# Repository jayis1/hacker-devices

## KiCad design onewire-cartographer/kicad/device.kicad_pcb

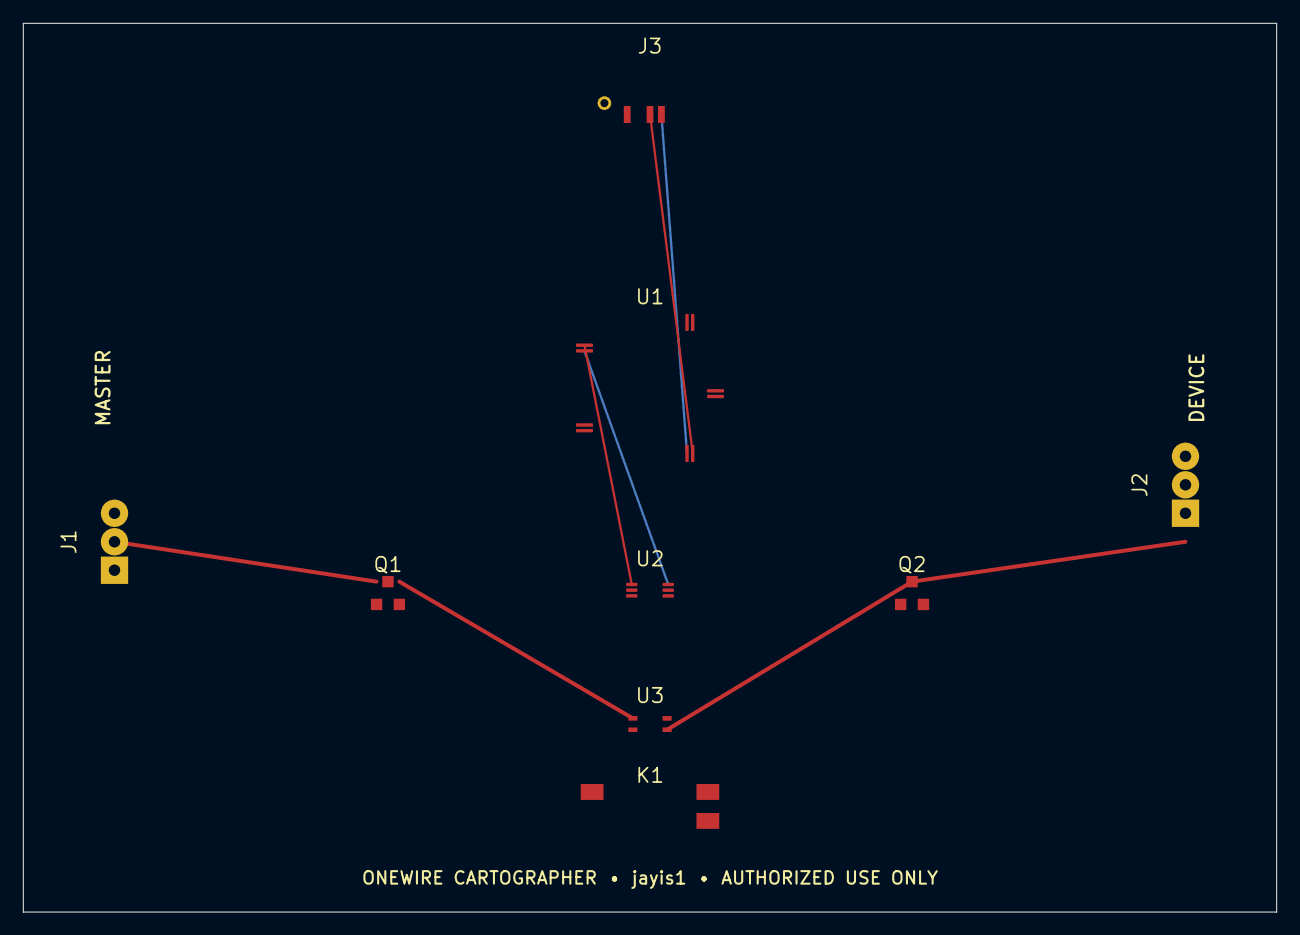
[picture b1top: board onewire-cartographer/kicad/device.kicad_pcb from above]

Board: 4 copper layers, 110.0 x 78.0 mm, 9 parts (0 on the bottom side), 12 nets.

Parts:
J1: MASTER; JST_XH_B3B-XH-A_1x03_P2.50mm_Vertical
J2: DEVICE; JST_XH_B3B-XH-A_1x03_P2.50mm_Vertical
J3: USB-C; USB_C_Receptacle_GCT_USB4105-xx-A_16P_TopMnt_Horizontal
K1: NC FAIL-OPEN BYPASS; Relay_DPDT_Omron_G6K-2F-Y
Q1, Q2: 2N7002; SOT-23
U1: STM32G474RET6; LQFP-64_10x10mm_P0.5mm
U2: TLV3502; VSSOP-8_2.3x2mm_P0.5mm
U3: TS5A23157; Texas_DRC0010J

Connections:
+3V3: U1.63, U2.3, U2.8, U3.10
+5V_LIMITED: J1.1, J2.1
BRIDGE_ENABLE: K1.4, U1.25, U3.3
DEVICE_EDGE: U1.2, U2.7
DEVICE_PULL_GATE: Q2.1, U1.16
GND: J1.3, J2.3, J3.A1, Q1.2, Q2.2, U1.64
MASTER_EDGE: U1.1, U2.1
MASTER_PULL_GATE: Q1.1, U1.15
OW_DEVICE_DQ: J2.2, K1.8, Q2.3, U2.5, U3.8
OW_MASTER_DQ: J1.2, K1.1, Q1.3, U2.2, U3.1
USB_DM: J3.A7, U1.34
USB_DP: J3.A6, U1.33

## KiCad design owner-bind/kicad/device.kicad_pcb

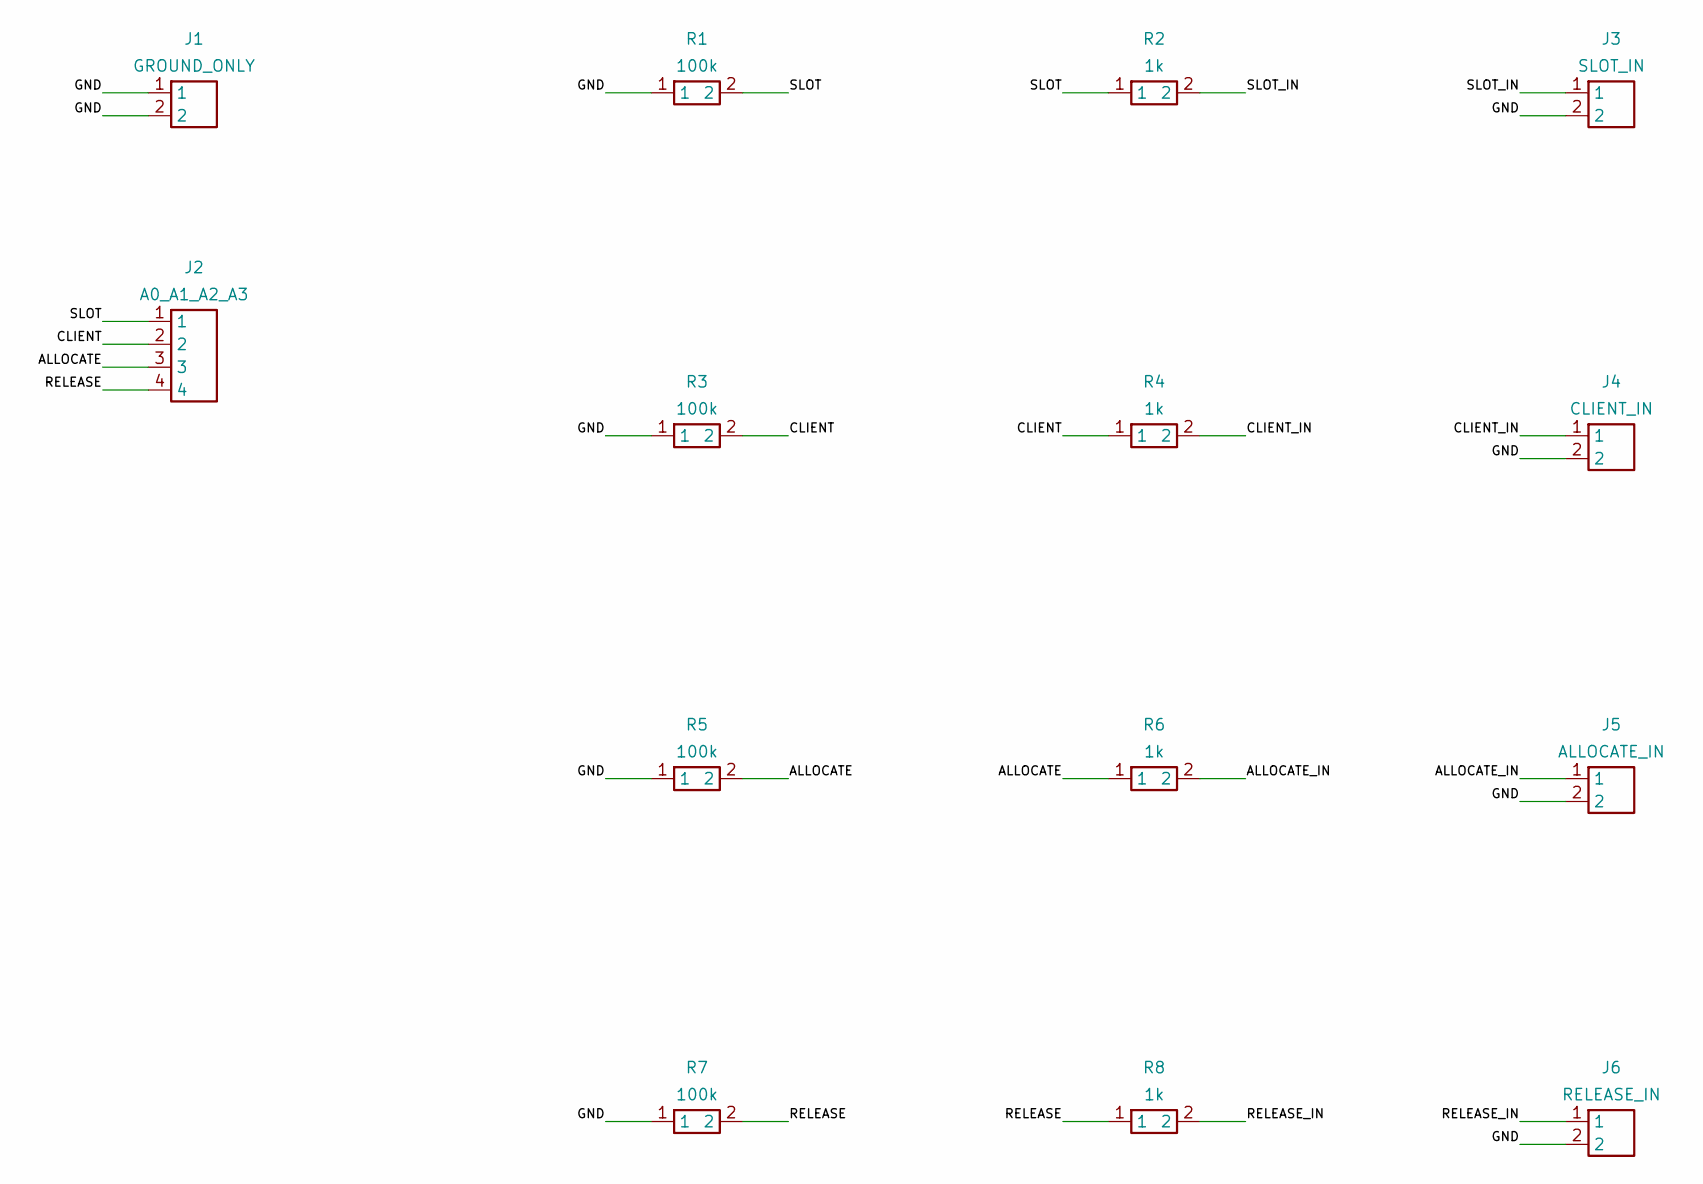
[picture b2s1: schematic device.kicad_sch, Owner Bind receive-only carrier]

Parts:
J1: GROUND_ONLY; PinHeader_1x02_P2.54mm_Vertical
J2: A0_A1_A2_A3; PinHeader_1x04_P2.54mm_Vertical
J3: SLOT_IN; PinHeader_1x02_P2.54mm_Vertical
J4: CLIENT_IN; PinHeader_1x02_P2.54mm_Vertical
J5: ALLOCATE_IN; PinHeader_1x02_P2.54mm_Vertical
J6: RELEASE_IN; PinHeader_1x02_P2.54mm_Vertical
R1, R3, R5, R7: 100k; R_Axial_DIN0207_L6.3mm_D2.5mm_P7.62mm_Horizontal
R2, R4, R6, R8: 1k; R_Axial_DIN0207_L6.3mm_D2.5mm_P7.62mm_Horizontal

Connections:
ALLOCATE: J2.3, R5.2, R6.1
ALLOCATE_IN: J5.1, R6.2
CLIENT: J2.2, R3.2, R4.1
CLIENT_IN: J4.1, R4.2
GND: J1.1, J1.2, J3.2, J4.2, J5.2, J6.2, R1.1, R3.1, R5.1, R7.1
RELEASE: J2.4, R7.2, R8.1
RELEASE_IN: J6.1, R8.2
SLOT: J2.1, R1.2, R2.1
SLOT_IN: J3.1, R2.2

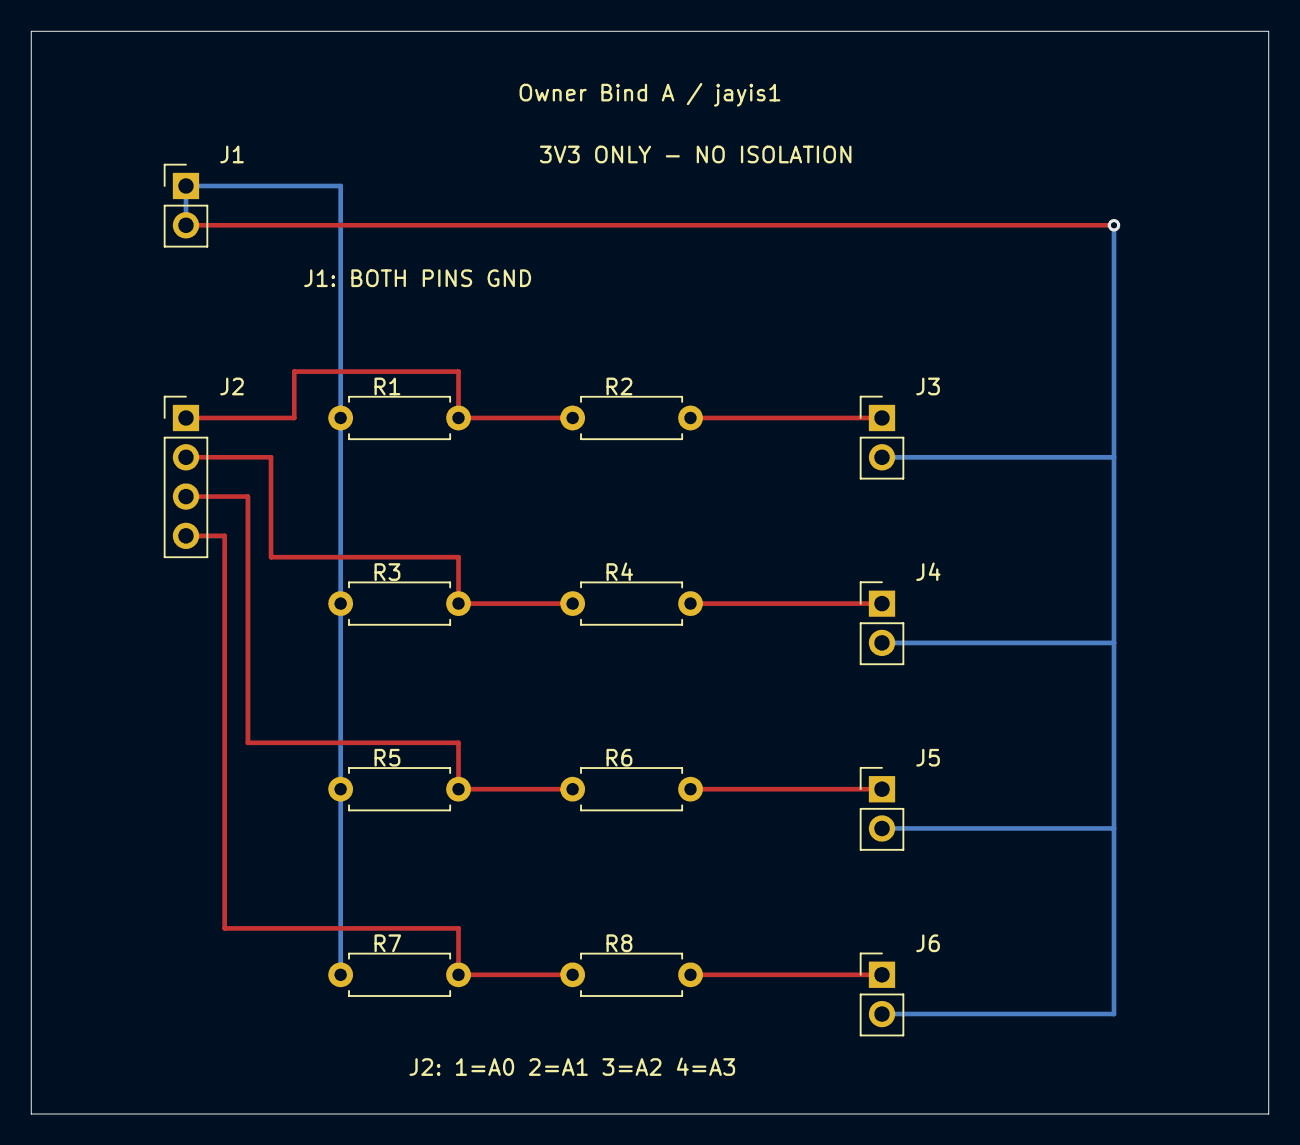
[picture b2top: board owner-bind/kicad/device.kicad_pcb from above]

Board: 2 copper layers, 80.0 x 70.0 mm, 14 parts (0 on the bottom side), 9 nets.

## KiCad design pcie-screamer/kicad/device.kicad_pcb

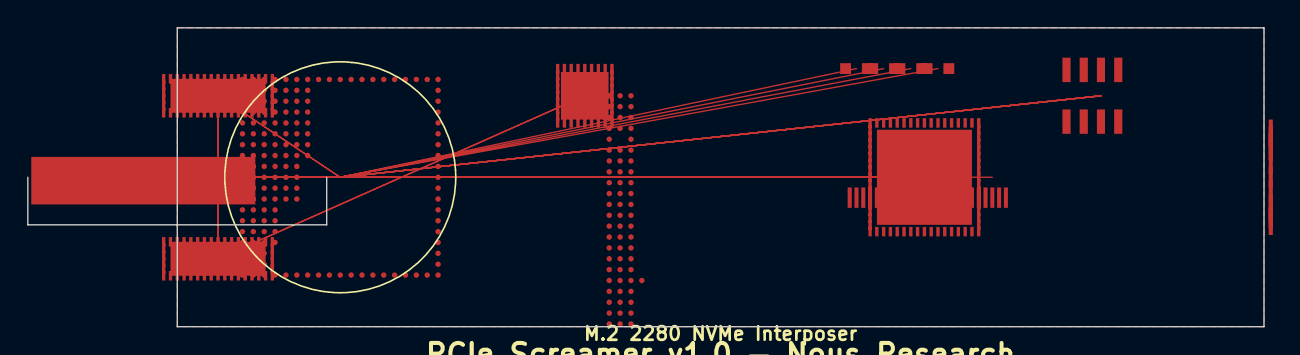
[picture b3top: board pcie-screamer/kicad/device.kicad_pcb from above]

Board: 8 copper layers, 80.0 x 22.0 mm, 14 parts (0 on the bottom side), 70 nets.

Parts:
D1: Green; LED_0603_1608Metric
D2: Blue; LED_0603_1608Metric
D3: Amber; LED_0603_1608Metric
D4: Red; LED_0603_1608Metric
J1: M.2_M-Key_Edge; M2_Edge_M_Key
J2: 10132797-0011LF; M2_Socket_M_Key
J3: TYPE-C-31-M-12; USB_C_Receptacle_16pin
U1: LFE5U-45F-6BG381C; BGA-381_17.0x17.0mm_Layout19x19_P0.8mm
U2, U3: PI3EQX12908ZHE; TQFN-42-1EP_9x3.5mm_P0.5mm
U4: FT601Q-B-T; QFN-76-1EP_9x9mm_P0.5mm
U5: MT41K256M16TW-107; FBGA-96_9.0x14.0mm_Layout9x16_P0.8mm
U6: W25Q128JVSIQ; SOIC-8_5.23x5.23mm_P1.27mm
U7: Si5332A-D-GM1; QFN-32-1EP_5x5mm_P0.5mm

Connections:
+1V2: U1.VCCIO_B4_5_7, U4.47, U4.48, U4.62, U4.63
+1V8: U1.VCCAUX, U1.VCCA_PLL
+1V35: U1.VCCIO_B6, U5.B7, U5.D3, U5.D8, U5.E1, U5.F9, U5.G1, U5.G9, U5.H1, U5.H9, U5.L1, U5.L9, U5.M1, U5.M9, U5.N1, U5.N9, U5.P1, U5.P9, U5.R1, U5.R9
+3V3: J1.2, J1.4, J1.70, J1.72, J1.74, J2.3V3, U1.C6, U1.C7, U1.D6, U1.D7, U1.E2, U1.F2, U1.G2, U1.H2, U1.J2, U1.K2, U1.L2, U1.M2, U1.VCCIO_B0_3, U2.1, U2.11, U2.21, U2.31, U3.1, U3.11, U3.21, U3.31, U4.5, U4.6, U4.7, U4.8, U4.9, U4.43, U4.44, U6.3, U6.7, U6.8, U7.5, U7.6, U7.7, U7.8
+3V3A: U4.49, U4.50
+5V0: J3.VBUS, U4.55
CLKREQ#: J1.52, J2.CLKREQ#, U1.AR2, U1.D5
DDR3_A[14:0]: U1.AA1, U1.AA2, U1.AA3, U1.U1, U1.U2, U1.U3, U1.V1, U1.V2, U1.V3, U1.W1, U1.W2, U1.W3, U1.Y1, U1.Y2, U1.Y3, U5.L7, U5.M2, U5.M3, U5.M7, U5.N2, U5.N3, U5.N7, U5.N8, U5.P3, U5.P8, U5.R3, U5.R7, U5.R8, U5.T3, U5.T8
DDR3_BA[2:0]: U1.AB1, U1.AB2, U1.AB3, U5.M6, U5.P2, U5.P7
DDR3_CAS#: U1.AM1, U5.K3
DDR3_CKE: U1.AL1, U5.K9
DDR3_CK_N: U1.AK3, U5.J7
DDR3_CK_P: U1.AK2, U5.K7
DDR3_CS#: U1.AL2, U5.L2
DDR3_DM[1:0]: U1.AJ3, U1.AK1, U5.D1, U5.E3
DDR3_DQS0_N: U1.AH3, U5.F3
DDR3_DQS0_P: U1.AH2, U5.F2
DDR3_DQS1_N: U1.AJ2, U5.B3
DDR3_DQS1_P: U1.AJ1, U5.B2
DDR3_DQ[15:0]: U1.AC1, U1.AC2, U1.AC3, U1.AD1, U1.AD2, U1.AD3, U1.AE1, U1.AE2, U1.AE3, U1.AF1, U1.AF2, U1.AF3, U1.AG1, U1.AG2, U1.AG3, U1.AH1, U5.A2, U5.A3, U5.A7, U5.A8, U5.B1, U5.B8, U5.C2, U5.C3, U5.C8, U5.D7, U5.E7, U5.E8, U5.F7, U5.F8, U5.G7, U5.G8
DDR3_ODT: U1.AM3, U5.K1
DDR3_RAS#: U1.AL3, U5.J3
DDR3_RESET#: U1.AN1, U5.T2
DDR3_WE#: U1.AM2, U5.L3
FT_BE[3:0]: U1.E7, U1.F7, U1.G7, U1.H7, U4.18, U4.70, U4.71, U4.76
FT_CLK: U1.M1, U4.35
FT_D[31:0]: U1.E3, U1.E4, U1.E5, U1.E6, U1.F3, U1.F4, U1.F5, U1.F6, U1.G3, U1.G4, U1.G5, U1.G6, U1.H3, U1.H4, U1.H5, U1.H6, U1.J3, U1.J4, U1.J5, U1.J6, U1.K3, U1.K4, U1.K5, U1.K6, U1.L3, U1.L4, U1.L5, U1.L6, U1.M3, U1.M4, U1.M5, U1.M6, U4.1, U4.2, U4.3, U4.4, U4.10, U4.11, U4.12, U4.13, U4.14, U4.15, U4.16, U4.17, U4.19, U4.20, U4.21, U4.22, U4.23, U4.24, U4.25, U4.26, U4.27, U4.28, U4.29, U4.30, U4.31, U4.32, U4.33, U4.34, U4.72, U4.73, U4.74, U4.75
FT_OE#: U1.J1, U4.42
FT_RD#: U1.H1, U4.41
FT_RESET#: U1.L1, U4.36
FT_RXF#: U1.F1, U4.39
FT_SIWU#: U1.K1, U4.37
FT_TXE#: U1.E1, U4.38
FT_WR#: U1.G1, U4.40
GND: D1.2, D2.2, D3.2, D4.2, J1.1, J1.3, J1.9, J1.15, J1.21, J1.27, J1.33, J1.39, J1.45, J1.51, J1.57, J1.71, J1.73, J1.75, J2.GND, J3.CC1, J3.CC2, J3.GND, J3.GND2, U1.A1, U1.A2, U1.B1, U1.B2, U1.C1, U1.C2, U1.D1, U1.D2, U2.6, U2.16, U2.26, U2.36, U2.EP, U3.6, U3.16, U3.26, U3.36, U3.EP, U4.45, U4.46, U4.51, U4.52, U4.56, U4.57, U4.58, U4.59, U4.60, U4.61, U4.64, U4.65, U4.67, U4.69, U4.EP, U5.A1, U5.A9, U5.B9, U5.C1, U5.C9, U5.D2, U5.D9, U5.E9, U5.F1, U5.G2, U5.G3, U5.H2, U5.H3, U5.H7, U5.H8, U5.J2, U5.J8, U5.J9, U5.K2, U5.K8, U5.L8, U5.M8, U5.R2, U5.T1, U5.T9, U6.4, U7.1, U7.2, U7.3, U7.4, U7.9, U7.10, U7.11, U7.12, U7.13, U7.14, U7.15, U7.16, U7.17, U7.18, U7.19, U7.20, U7.21, U7.22, U7.23, U7.24, U7.27, U7.28, U7.31, U7.32, U7.EP
I2C_SCL: U1.A6, U1.A7, U2.41, U3.41, U7.25
I2C_SDA: U1.B6, U1.B7, U2.42, U3.42, U7.26
LED0: D1.1, U1.A4
LED1: D2.1, U1.B4
LED2: D3.1, U1.C4
LED3: D4.1, U1.D4
PCIE_REFCLK_N: J1.53, J2.REFCLKn, U1.AP2, U7.29
PCIE_REFCLK_P: J1.55, J2.REFCLKp, U1.AP1, U7.30
PCIE_RX0_N: J1.41, J2.PERn0, U1.N2, U2.3, U2.5
PCIE_RX0_P: J1.43, J2.PERp0, U1.N1, U2.2, U2.4
PCIE_RX1_N: J1.29, J2.PERn1, U1.N4, U2.8, U2.10, U2.33, U2.35
PCIE_RX1_P: J1.31, J2.PERp1, U1.N3, U2.7, U2.9, U2.32, U2.34
PCIE_RX2_N: J1.17, J2.PERn2, U1.R2, U3.3, U3.5
PCIE_RX2_P: J1.19, J2.PERp2, U1.R1, U3.2, U3.4
PCIE_RX3_N: J1.5, J2.PERn3, U1.R4, U3.8, U3.10, U3.33, U3.35
PCIE_RX3_P: J1.7, J2.PERp3, U1.R3, U3.7, U3.9, U3.32, U3.34
PCIE_TX0_N: J1.47, J2.PETn0, U1.P2, U2.13, U2.15, U2.23, U2.25
PCIE_TX0_P: J1.49, J2.PETp0, U1.P1, U2.12, U2.14, U2.22, U2.24
PCIE_TX1_N: J1.35, J2.PETn1, U1.P4, U2.18, U2.20, U2.28, U2.30, U2.38, U2.40
PCIE_TX1_P: J1.37, J2.PETp1, U1.P3, U2.17, U2.19, U2.27, U2.29, U2.37, U2.39
PCIE_TX2_N: J1.23, J2.PETn2, U1.T2, U3.13, U3.15, U3.23, U3.25
PCIE_TX2_P: J1.25, J2.PETp2, U1.T1, U3.12, U3.14, U3.22, U3.24
PCIE_TX3_N: J1.11, J2.PETn3, U1.T4, U3.18, U3.20, U3.28, U3.30, U3.38, U3.40
PCIE_TX3_P: J1.13, J2.PETp3, U1.T3, U3.17, U3.19, U3.27, U3.29, U3.37, U3.39
PERST#: J1.50, J2.PERST#, U1.AR1, U1.C5
PEWAKE#: J1.54, J2.PEWAKE#, U1.AR3
SPI_CLK: U1.B3, U6.6
SPI_CS#: U1.A3, U6.1
SPI_MISO: U1.D3, U6.2
SPI_MOSI: U1.C3, U6.5
SUSCLK: J1.68, J2.SUSCLK
USB_DM: J3.D-, U4.53
USB_DP: J3.D+, U4.54
USB_SSRX_N: J3.SSRX-, U4.66
USB_SSRX_P: J3.SSRX+, U4.68

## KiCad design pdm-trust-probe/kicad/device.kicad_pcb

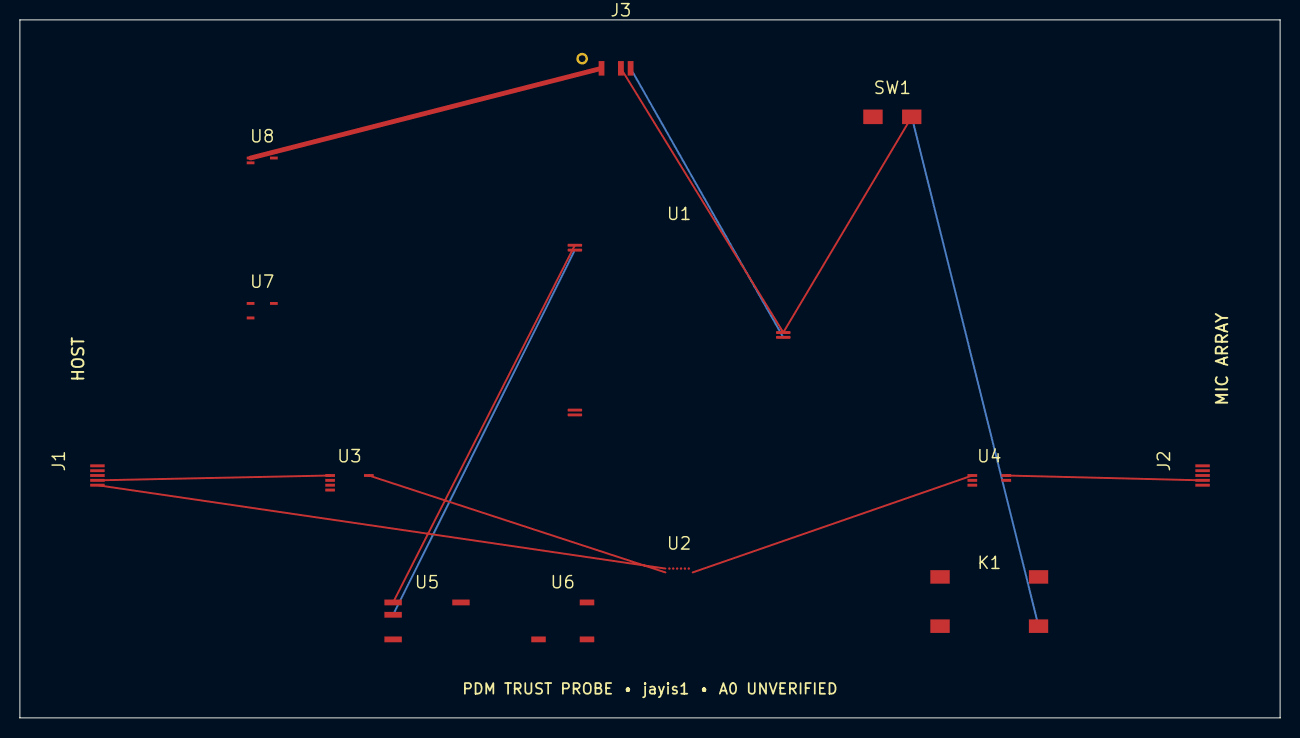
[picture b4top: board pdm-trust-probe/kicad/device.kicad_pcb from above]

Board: 4 copper layers, 130.0 x 72.0 mm, 13 parts (0 on the bottom side), 13 nets.

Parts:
J1: HOST PDM; TE_1-1734592-0_1x10-1MP_P0.5mm_Horizontal
J2: MIC PDM; TE_1-1734592-0_1x10-1MP_P0.5mm_Horizontal
J3: USB-C; USB_C_Receptacle_GCT_USB4105-xx-A_16P_TopMnt_Horizontal
K1: FAIL-SAFE BYPASS; Relay_DPDT_Omron_G6K-2F-Y
SW1: PHYSICAL ARM; SW_SPST_TL3301AN
U1: STM32H563ZIT6; LQFP-144_20x20mm_P0.5mm
U2: iCE40UP5K-SG48; ucBGA-48_3.0x3.0mm_Layout6x8_P0.4mm
U3: SN74AXC4T245; UQFN-14-1EP_3.5x2.5mm_P0.5mm_EP0.6x2.6mm
U4: TMUX1574; WQFN-16-1EP_3x3mm_P0.5mm_EP1.75x1.75mm
U5: MX25L12835F; SOIC-8_5.23x5.23mm_P1.27mm
U6: ATECC608B; SOIC-8_3.9x4.9mm_P1.27mm
U7: ADS7042; WSON-8-1EP_2x2mm_P0.5mm_EP0.6x1.2mm
U8: TPS62172; WSON-8-1EP_2x2mm_P0.5mm_EP0.6x1.2mm

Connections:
+3V3: U1.143, U3.14, U5.8, U6.8, U7.8, U8.8
GND: J3.A1, K1.2, SW1.1, U1.144, U5.4, U6.4, U7.4, U8.2
PATTERN_ENABLE: K1.7, SW1.2, U4.15
PDM_CLK: J1.1, J2.1, K1.1, K1.8, U2.A1
PDM_DATA0: J1.2, J2.2, U2.B1, U3.2, U4.1
PDM_DATA1: J1.3, J2.3, U2.C1, U3.3, U4.2
PDM_DATA2: J1.4, J2.4, U2.D1, U3.4, U4.3
PDM_DATA3: J1.5, J2.5, U2.E1, U3.5, U4.14
SPI_CLK: U1.1, U5.1
SPI_DATA: U1.2, U5.2, U6.5
USB_DM: J3.A7, U1.71
USB_DP: J3.A6, U1.70
VBUS: J3.A4, U8.1

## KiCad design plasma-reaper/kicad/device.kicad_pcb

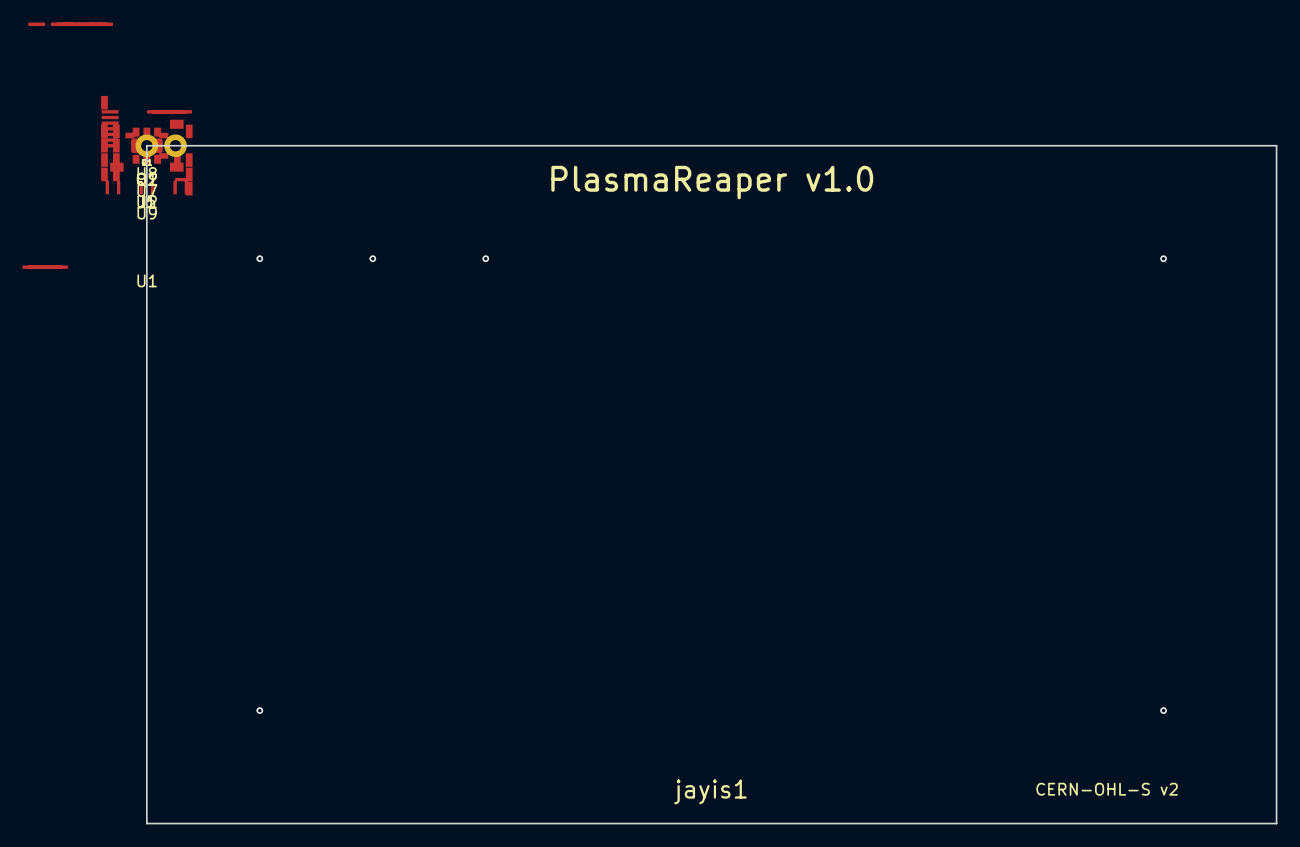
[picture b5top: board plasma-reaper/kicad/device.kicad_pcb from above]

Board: 2 copper layers, 100.0 x 60.0 mm, 11 parts (0 on the bottom side), 17 nets.

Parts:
C1: 100nF; C_0603_1608Metric
J1: USB_C_Receptacle; USB_C_Receptacle_HRO_TYPE-C-31-M-12
J5: BNC; BNC_Amphenol_031-6535_Horizontal
Q1: SiS413DN; PowerPAK_1212-8_Single
Q2: BSC060N10NS3G; TDSON-8-1
R1: 0R5; R_0805_2012Metric
U1: STM32H723ZGT6; LQFP-144_20x20mm_P0.5mm
U2: iCE40UP5K-SG48; QFN-48-1EP_7x7mm_P0.5mm_EP5.6x5.6mm
U7: ZXGD3004E1; SOIC-8_3.9x9.9mm_P1.27mm
U8: DAC5311; SOT-23-6
U9: TS3A5018; SOIC-16_3.9x9.9mm_P1.27mm

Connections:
+3V3: C1.1, U1.11, U1.19, U1.28, U1.30, U2.1, U8.3, U9.16
+5V: Q2.2, U7.1
EM_COIL+: J5.1, U7.6
EM_COIL-: J5.2, U7.4
EM_GATE: U2.5, U7.2
FPGA_NSS: U1.39, U2.28
GND: C1.2, J1.A1, J1.B1, Q1.2, U1.10, U1.27, U1.29, U1.49, U2.24, U7.3, U8.4, U9.8
MUX_SEL0: U2.6, U9.14
MUX_SEL1: U2.7, U9.13
SHUNT_GATE: Q1.1, U2.4
SPI1_MISO: U1.41, U2.25
SPI1_MOSI: U1.42, U2.26, U8.2
SPI1_SCK: U1.40, U2.27, U8.1
USB_DM: J1.A7, U1.46
USB_DP: J1.A6, U1.47
VBUS: J1.A4, J1.B4
VCC_TARGET: Q1.3, Q2.3, R1.1

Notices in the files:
nvme-phantom/kicad/device.kicad_sch:
License: CERN-OHL-S v2
plasma-reaper/kicad/device.kicad_pcb:
CERN-OHL-S v2
